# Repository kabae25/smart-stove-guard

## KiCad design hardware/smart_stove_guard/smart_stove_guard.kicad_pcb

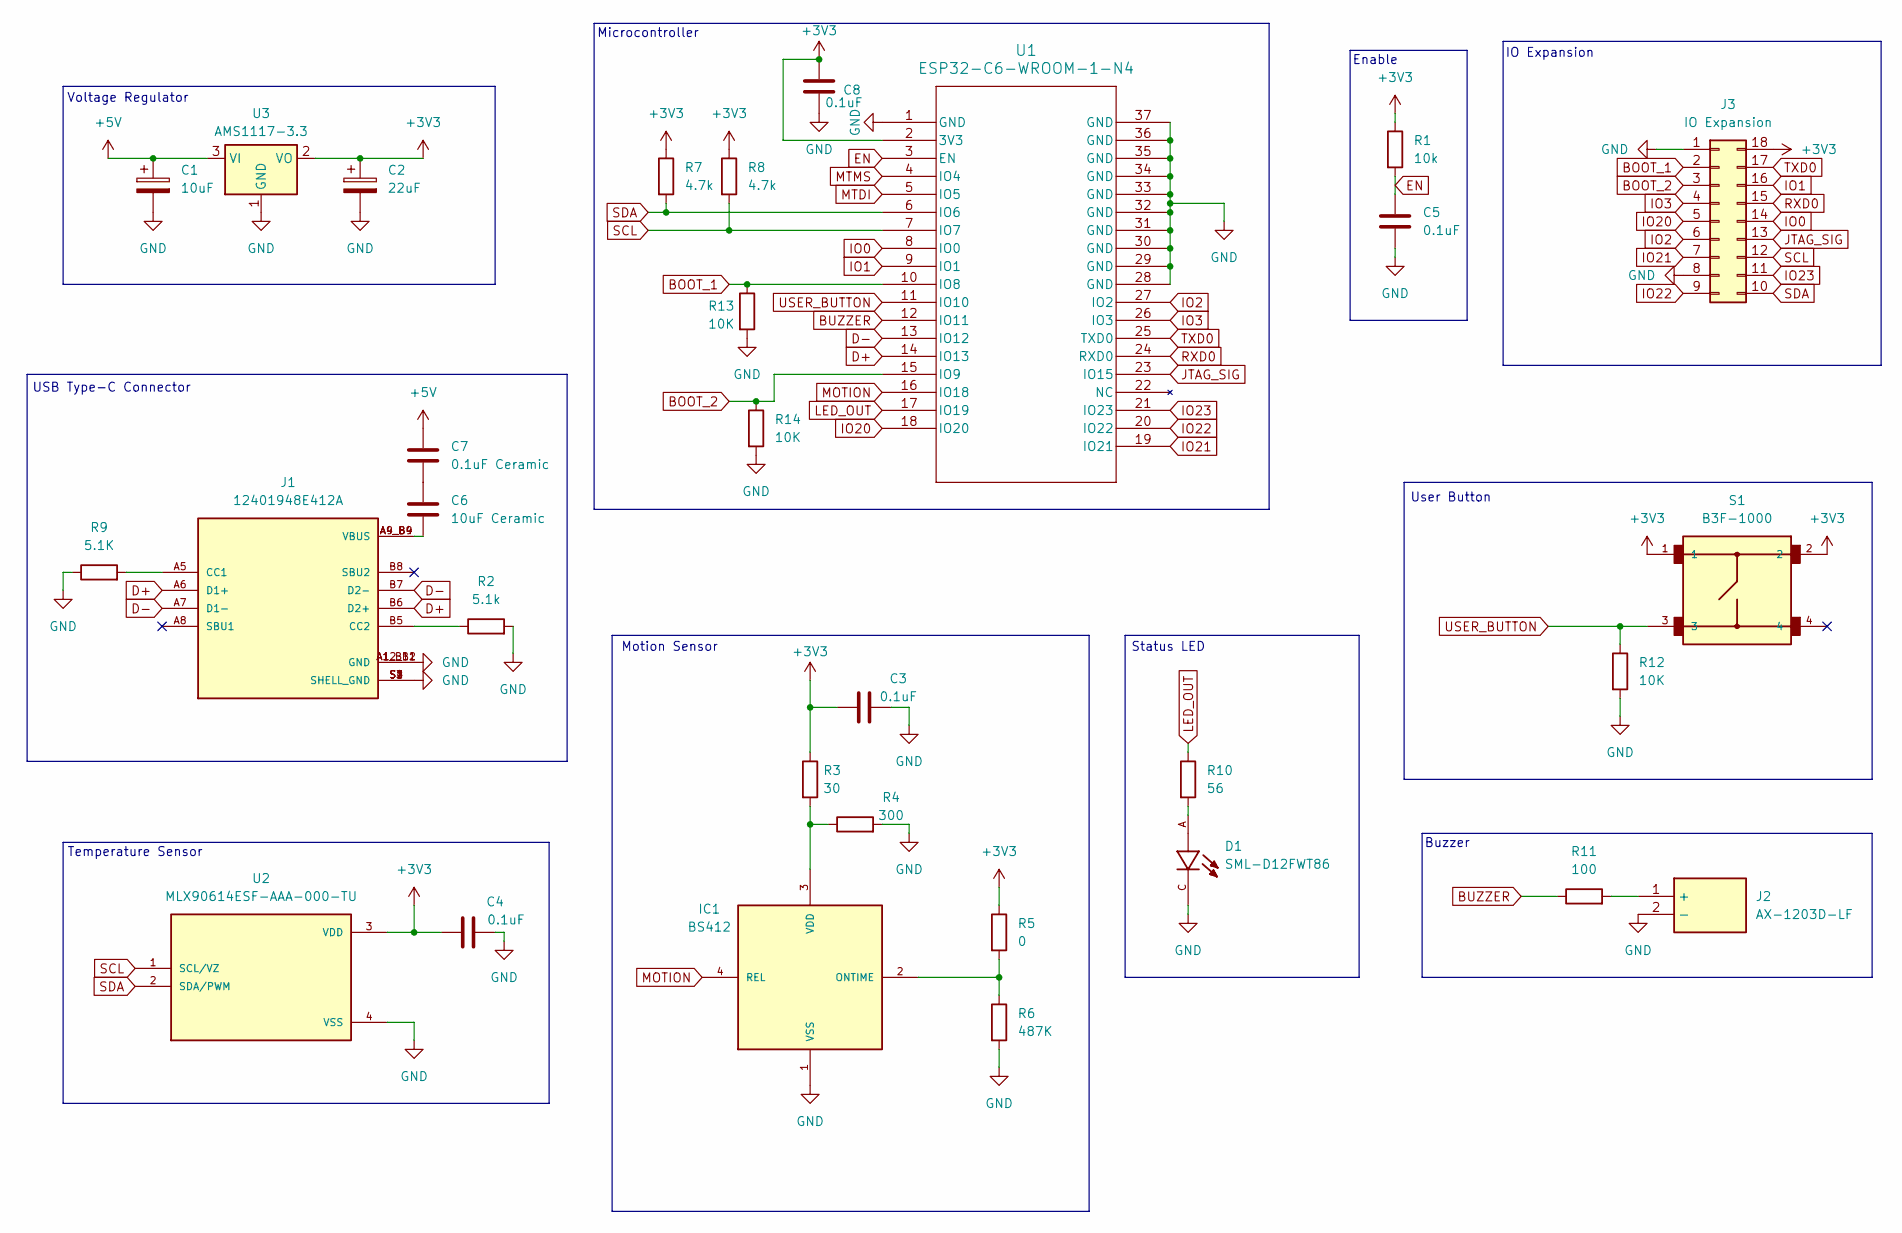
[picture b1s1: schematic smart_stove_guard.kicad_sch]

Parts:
C1: 10uF; CP_EIA-3216-10_Kemet-I_HandSolder
C2: 22uF; CP_EIA-3216-10_Kemet-I_HandSolder
C3, C4, C5, C8: 0.1uF; C_0805_2012Metric
C6: 10uF Ceramic; C_0805_2012Metric
C7: 0.1uF Ceramic; C_0805_2012Metric
D1: SML-D12FWT86; LED_SML-D12FWT86; PARTREV 007
IC1: BS412; MANUFACTURER_PART_NUMBER BS412
J1: 12401948E412A; AMPHENOL_12401948E412A; PARTREV 3
J2: AX-1203D-LF; AX1203DLF; Mouser Part Number 253-AX1203DLF
J3: IO Expansion; PinSocket_2x09_P2.54mm_Vertical
R1: 10k; R_0805_2012Metric
R2: 5.1k; R_0805_2012Metric
R3: 30; R_0805_2012Metric
R4: 300; R_0805_2012Metric
R5: 0; R_0805_2012Metric
R6: 487K; R_0805_2012Metric
R7, R8: 4.7k; R_0805_2012Metric
R9: 5.1K; R_0805_2012Metric
R10: 56; R_0805_2012Metric
R11: 100; R_0805_2012Metric
R12, R13, R14: 10K; R_0805_2012Metric
S1: B3F-1000; SW_B3F-1000
U1: ESP32-C6-WROOM-1-N4; MOD28_ESP32-C6-WROOM-1_EXP
U2: MLX90614ESF-AAA-000-TU; MLX90614ESF-AAA-000; PARTREV 13
U3: AMS1117-3.3; SOT-223-3_TabPin2

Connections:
+3V3: C2.1, C3.2, C4.2, C8.1, J3.18, R1.1, R3.1, R5.1, R7.1, R8.1, S1.1, S1.2, U1.2 (3V3), U2.3 (VDD), U3.2 (VO)
+5V: C1.1, C7.1, U3.3 (VI)
BOOT_1: J3.2, R13.1, U1.10 (IO8)
BOOT_2: J3.3, R14.1, U1.15 (IO9)
BUZZER: R11.1, U1.12 (IO11)
D+: J1.A6 (D1+), J1.B6 (D2+), U1.14 (IO13)
D-: J1.A7 (D1-), J1.B7 (D2-), U1.13 (IO12)
EN: C5.1, R1.2, U1.3 (EN)
GND: C1.2, C2.2, C3.1, C4.1, C5.2, C8.2, D1.C, IC1.1 (VSS), J1.A1_B12 (GND), J1.A12_B1 (GND), J1.S1 (SHELL_GND), J1.S2 (SHELL_GND), J1.S3 (SHELL_GND), J1.S4 (SHELL_GND), J2.2 (-), J3.1, J3.8, R2.2, R4.2, R6.2, R9.1, R12.2, R13.2, R14.2, U1.1 (GND), U1.28 (GND), U1.29 (GND), U1.30 (GND), U1.31 (GND), U1.32 (GND), U1.33 (GND), U1.34 (GND), U1.35 (GND), U1.36 (GND), U1.37 (GND), U2.4 (VSS), U3.1 (GND)
IO0: J3.14, U1.8 (IO0)
IO1: J3.16, U1.9 (IO1)
IO2: J3.6, U1.27 (IO2)
IO3: J3.4, U1.26 (IO3)
IO20: J3.5, U1.18 (IO20)
IO21: J3.7, U1.19 (IO21)
IO22: J3.9, U1.20 (IO22)
IO23: J3.11, U1.21 (IO23)
JTAG_SIG: J3.13, U1.23 (IO15)
LED_OUT: R10.1, U1.17 (IO19)
MOTION: IC1.4 (REL), U1.16 (IO18)
MTDI: U1.5 (IO5)
MTMS: U1.4 (IO4)
unnamed: C6.1, C7.2
unnamed: C6.2, J1.A4_B9 (VBUS), J1.A9_B4 (VBUS)
unnamed: D1.A, R10.2
unnamed: IC1.2 (ONTIME), R5.2, R6.1
unnamed: IC1.3 (VDD), R3.2, R4.1
unnamed: J1.A5 (CC1), R9.2
unnamed: J1.B5 (CC2), R2.1
unnamed: J2.1 (+), R11.2
RXD0: J3.15, U1.24 (RXD0)
SCL: J3.12, R8.2, U1.7 (IO7), U2.1 (SCL/VZ)
SDA: J3.10, R7.2, U1.6 (IO6), U2.2 (SDA/PWM)
TXD0: J3.17, U1.25 (TXD0)
USER_BUTTON: R12.1, S1.3, U1.11 (IO10)

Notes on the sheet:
Status LED
Temperature Sensor
Microcontroller
Buzzer
Enable
Voltage Regulator
IO Expansion
USB Type-C Connector
User Button
Motion Sensor

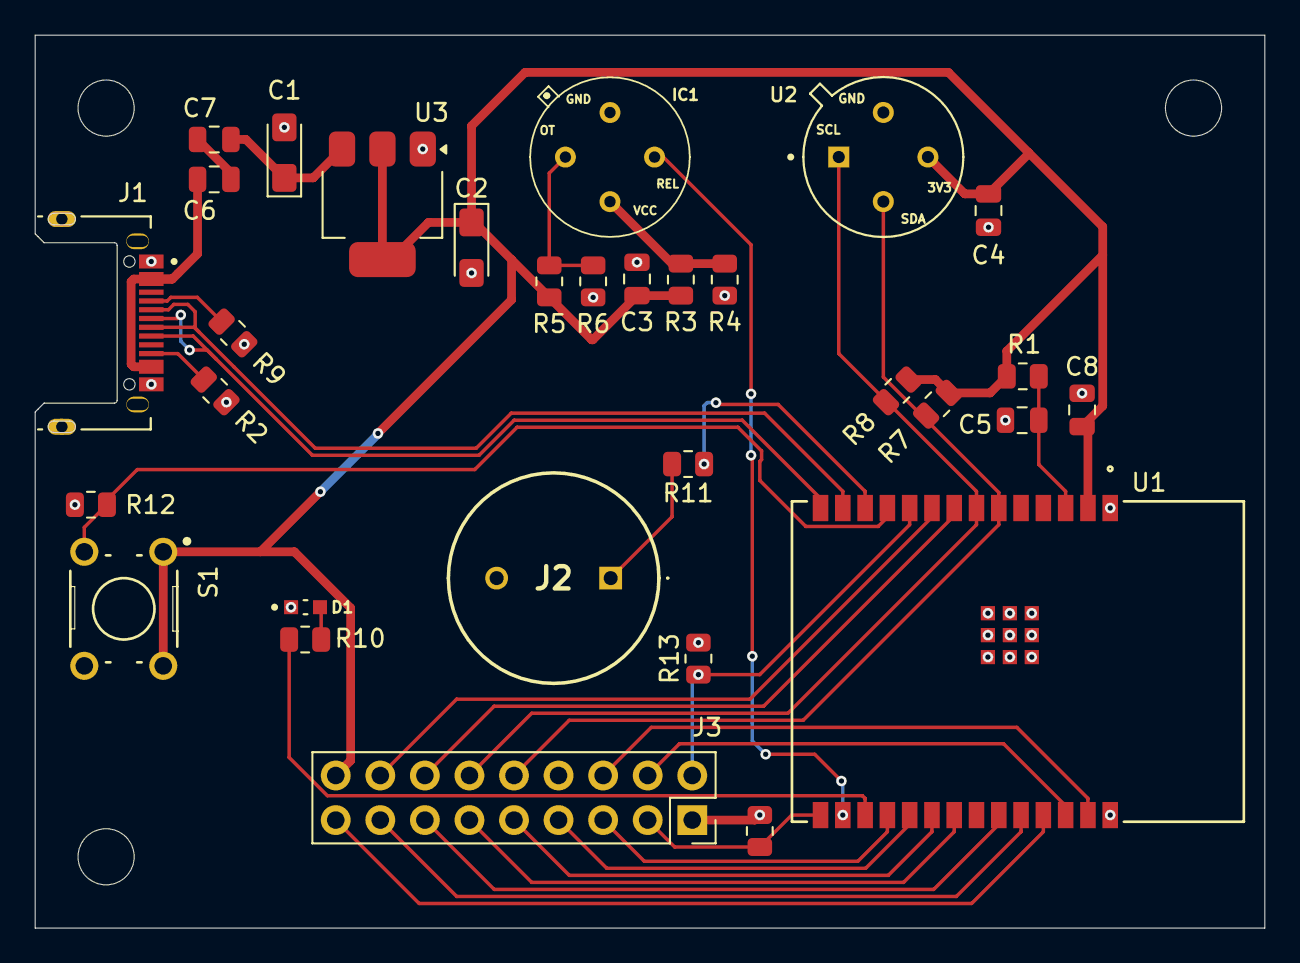
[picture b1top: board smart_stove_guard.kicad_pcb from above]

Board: 2 copper layers, 70.1 x 50.9 mm, 31 parts (0 on the bottom side), 33 nets.

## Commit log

2025-04-11 init
2025-04-11 kicad project file
2025-04-14 made platform io project
2025-04-14 init arduino projects
2025-04-16 Post Design Review 3
2025-04-17 Getting schematic ready for pcb + some code changes
2025-04-17 Finished initial schematic, added footprints and symbols for missing components
2025-04-17 Finished Schematic, going to send to TA for look over
2025-04-21 Updated footprints
2025-04-21 Signal Lines + Basic Layout
2025-04-24 minor changes before continuing layout tonight
2025-04-25 Waiting for IFTTT changes
2025-04-27 ground pours and mounting
2025-04-27 Done with layout
2025-04-27 Finished layout, but going to skip for time and budget
2025-04-29 Initialized ESP-IDF and started working on the project
2025-04-30 added blynk functionality
2025-04-30 statemachine implemented
2025-05-05 statemachine tested. Waiting on Motion Sensor and Blynk
2025-05-07 Blynk functionality
2025-05-07 Full functionality
2025-05-07 end of term cleanup
